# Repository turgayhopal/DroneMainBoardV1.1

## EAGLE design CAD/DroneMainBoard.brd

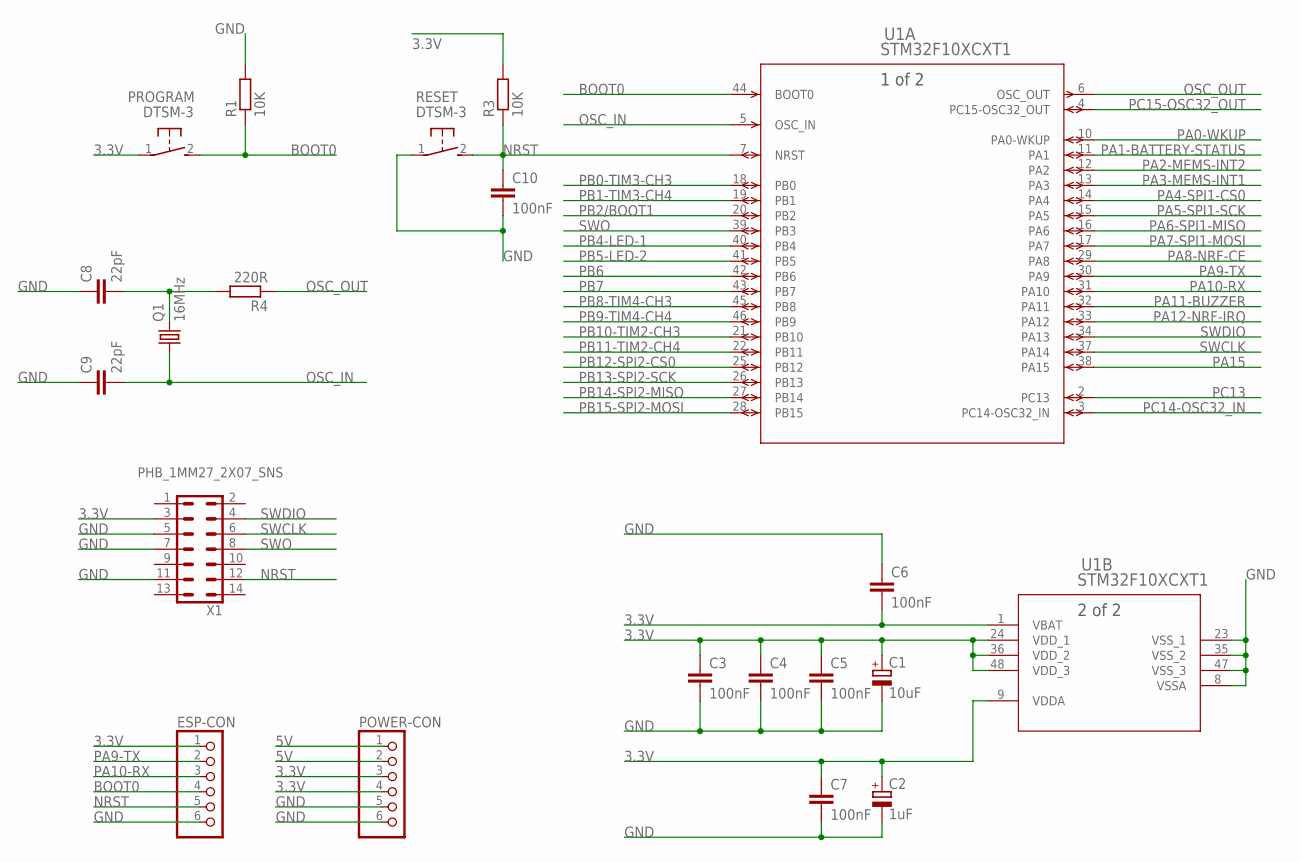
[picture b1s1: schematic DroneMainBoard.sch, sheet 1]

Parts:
C1: 10uF; SMC_A
C2: 1uF; SMC_A
C3, C4, C5, C6, C7, C10: 100nF; C0603
C8, C9: 22pF; C0603
ESP-CON: PINHD-1X6; 1X06
POWER-CON: PINHD-1X6; 1X06
PROGRAM: DTSM-3
Q1: 16MHz; HC49/S
R1, R3: 10K; R0603
R4: 220R; R0603
RESET: DTSM-3
U1: STM32F10XCXT1; LQFP48-7X7MM
X1: PHB_1MM27_2X07_SNS

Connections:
3.3V: C1.+, C2.+, C3.1, C4.1, C5.1, C6.2, C7.1, ESP-CON.1, POWER-CON.3, POWER-CON.4, PROGRAM.1, R3.2, U1.1 (VBAT), U1.9 (VDDA), U1.24 (VDD_1), U1.36 (VDD_2), U1.48 (VDD_3), X1.3; also elsewhere on the board
5V: POWER-CON.1, POWER-CON.2; also elsewhere on the board
BOOT0: ESP-CON.4, PROGRAM.2, R1.1, U1.44 (BOOT0)
GND: C1.-, C2.-, C3.2, C4.2, C5.2, C6.1, C7.2, C8.1, C9.1, C10.2, ESP-CON.6, POWER-CON.5, POWER-CON.6, R1.2, RESET.1, U1.8 (VSSA), U1.23 (VSS_1), U1.35 (VSS_2), U1.47 (VSS_3), X1.5, X1.7, X1.11; also elsewhere on the board
unnamed: C8.2, Q1.2, R4.2
NRST: C10.1, ESP-CON.5, R3.1, RESET.2, U1.7 (NRST), X1.12
OSC_IN: C9.2, Q1.1, U1.5 (OSC_IN)
OSC_OUT: R4.1, U1.6 (OSC_OUT)
PA0-WKUP: U1.10 (PA0-WKUP)
PA1-BATTERY-STATUS: U1.11 (PA1); also elsewhere on the board
PA2-MEMS-INT2: U1.12 (PA2); also elsewhere on the board
PA3-MEMS-INT1: U1.13 (PA3); also elsewhere on the board
PA4-SPI1-CS0: U1.14 (PA4); also elsewhere on the board
PA5-SPI1-SCK: U1.15 (PA5); also elsewhere on the board
PA6-SPI1-MISO: U1.16 (PA6); also elsewhere on the board
PA7-SPI1-MOSI: U1.17 (PA7); also elsewhere on the board
PA8-NRF-CE: U1.29 (PA8); also elsewhere on the board
PA9-TX: ESP-CON.2, U1.30 (PA9)
PA10-RX: ESP-CON.3, U1.31 (PA10)
PA11-BUZZER: U1.32 (PA11); also elsewhere on the board
PA12-NRF-IRQ: U1.33 (PA12); also elsewhere on the board
PA15: U1.38 (PA15)
PB0-TIM3-CH3: U1.18 (PB0)
PB1-TIM3-CH4: U1.19 (PB1)
PB2/BOOT1: U1.20 (PB2)
PB4-LED-1: U1.40 (PB4); also elsewhere on the board
PB5-LED-2: U1.41 (PB5); also elsewhere on the board
PB6: U1.42 (PB6)
PB7: U1.43 (PB7)
PB8-TIM4-CH3: U1.45 (PB8); also elsewhere on the board
PB9-TIM4-CH4: U1.46 (PB9); also elsewhere on the board
PB10-TIM2-CH3: U1.21 (PB10); also elsewhere on the board
PB11-TIM2-CH4: U1.22 (PB11); also elsewhere on the board
PB12-SPI2-CS0: U1.25 (PB12); also elsewhere on the board
PB13-SPI2-SCK: U1.26 (PB13); also elsewhere on the board
PB14-SPI2-MISO: U1.27 (PB14); also elsewhere on the board
PB15-SPI2-MOSI: U1.28 (PB15); also elsewhere on the board
PC13: U1.2 (PC13)
PC14-OSC32_IN: U1.3 (PC14-OSC32_IN)
PC15-OSC32_OUT: U1.4 (PC15-OSC32_OUT)
SWCLK: U1.37 (PA14), X1.6
SWDIO: U1.34 (PA13), X1.4
SWO: U1.39 (PB3), X1.8

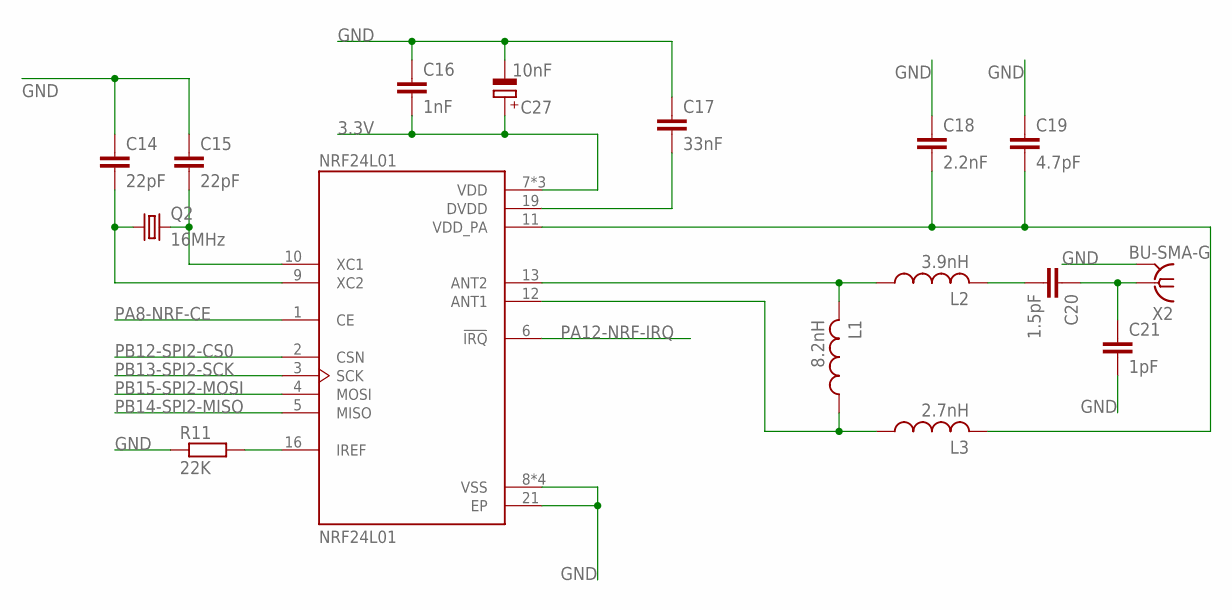
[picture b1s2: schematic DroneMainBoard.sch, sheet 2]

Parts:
C14, C15: 22pF; C0603
C16: 1nF; C0603
C17: 33nF; C0603
C18: 2.2nF; C0603
C19: 4.7pF; C0603
C20: 1.5pF; C0603
C21: 1pF; C0603
C27: 10nF; SMC_A
L1: 8.2nH; L2012C
L2: 3.9nH; L2012C
L3: 2.7nH; L2012C
NRF24L01: NRF24L01; QFN50P400X400X95-21N
Q2: 16MHz; HC49/S
R11: 22K; R0603
X2: BU-SMA-G

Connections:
3.3V: C16.2, C27.+, NRF24L01.7 (VDD), NRF24L01.15 (VDD), NRF24L01.18 (VDD); also elsewhere on the board
GND: C14.1, C15.1, C16.1, C17.1, C18.1, C19.1, C21.2, C27.-, NRF24L01.8 (VSS), NRF24L01.14 (VSS), NRF24L01.17 (VSS), NRF24L01.20 (VSS), NRF24L01.21 (EP), R11.1, X2.2, X2.3 (2), X2.4 (2), X2.5 (2); also elsewhere on the board
unnamed: NRF24L01.16 (IREF), R11.2
unnamed: C17.2, NRF24L01.19 (DVDD)
unnamed: L1.2, L2.1, NRF24L01.13 (ANT2)
unnamed: L1.1, L3.1, NRF24L01.12 (ANT1)
unnamed: C18.2, C19.2, L3.2, NRF24L01.11 (VDD_PA)
unnamed: C14.2, NRF24L01.9 (XC2), Q2.1
unnamed: C15.2, NRF24L01.10 (XC1), Q2.2
unnamed: C20.1, C21.1, X2.1
unnamed: C20.2, L2.2
PA8-NRF-CE: NRF24L01.1 (CE); also elsewhere on the board
PA12-NRF-IRQ: NRF24L01.6 (!IRQ); also elsewhere on the board
PB12-SPI2-CS0: NRF24L01.2 (CSN); also elsewhere on the board
PB13-SPI2-SCK: NRF24L01.3 (SCK); also elsewhere on the board
PB14-SPI2-MISO: NRF24L01.5 (MISO); also elsewhere on the board
PB15-SPI2-MOSI: NRF24L01.4 (MOSI); also elsewhere on the board

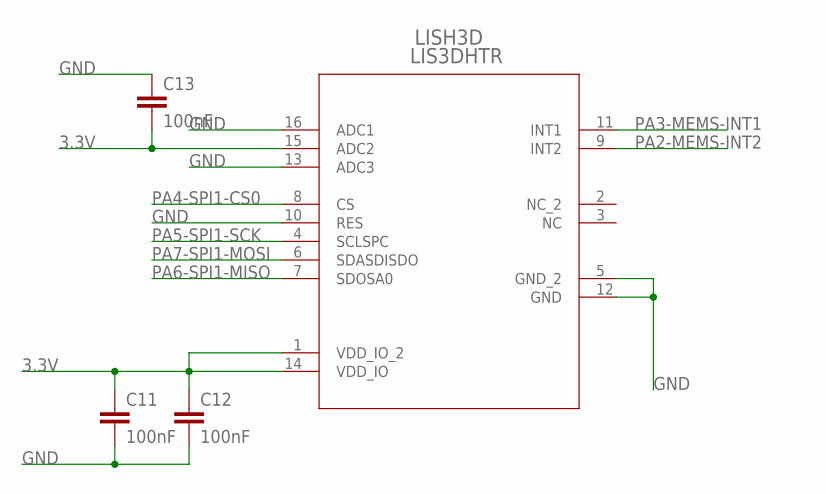
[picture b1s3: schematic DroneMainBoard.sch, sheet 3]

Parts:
C11, C12, C13: 100nF; C0603
LISH3D: LIS3DHTR; LGA-16_3X3X1MM_STM

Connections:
3.3V: C11.1, C12.1, C13.2, LISH3D.1 (VDD_IO_2), LISH3D.14 (VDD_IO), LISH3D.15 (ADC2); also elsewhere on the board
GND: C11.2, C12.2, C13.1, LISH3D.5 (GND_2), LISH3D.10 (RES), LISH3D.12 (GND), LISH3D.13 (ADC3), LISH3D.16 (ADC1); also elsewhere on the board
PA2-MEMS-INT2: LISH3D.9 (INT2); also elsewhere on the board
PA3-MEMS-INT1: LISH3D.11 (INT1); also elsewhere on the board
PA4-SPI1-CS0: LISH3D.8 (CS); also elsewhere on the board
PA5-SPI1-SCK: LISH3D.4 (SCLSPC); also elsewhere on the board
PA6-SPI1-MISO: LISH3D.7 (SDOSA0); also elsewhere on the board
PA7-SPI1-MOSI: LISH3D.6 (SDASDISDO); also elsewhere on the board

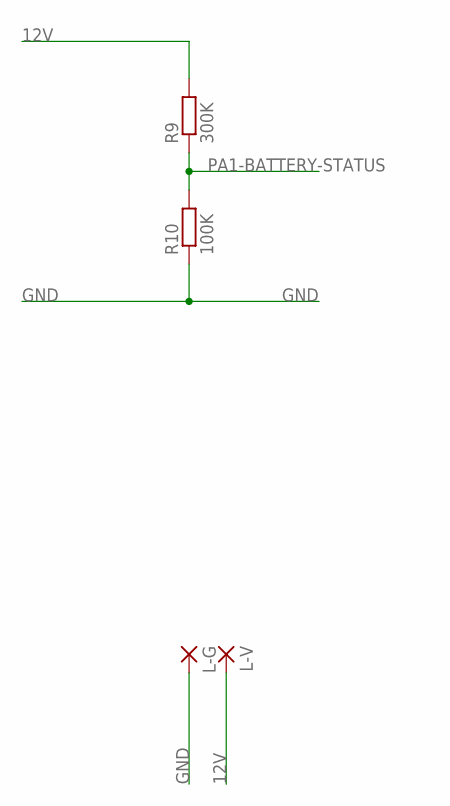
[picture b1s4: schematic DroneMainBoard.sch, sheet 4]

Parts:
L-G: 2,54/1,1
L-V: 2,54/1,1
R9: 300K; R0603
R10: 100K; R0603

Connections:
12V: L-V.1, R9.2
GND: L-G.1, R10.1; also elsewhere on the board
PA1-BATTERY-STATUS: R9.1, R10.2; also elsewhere on the board

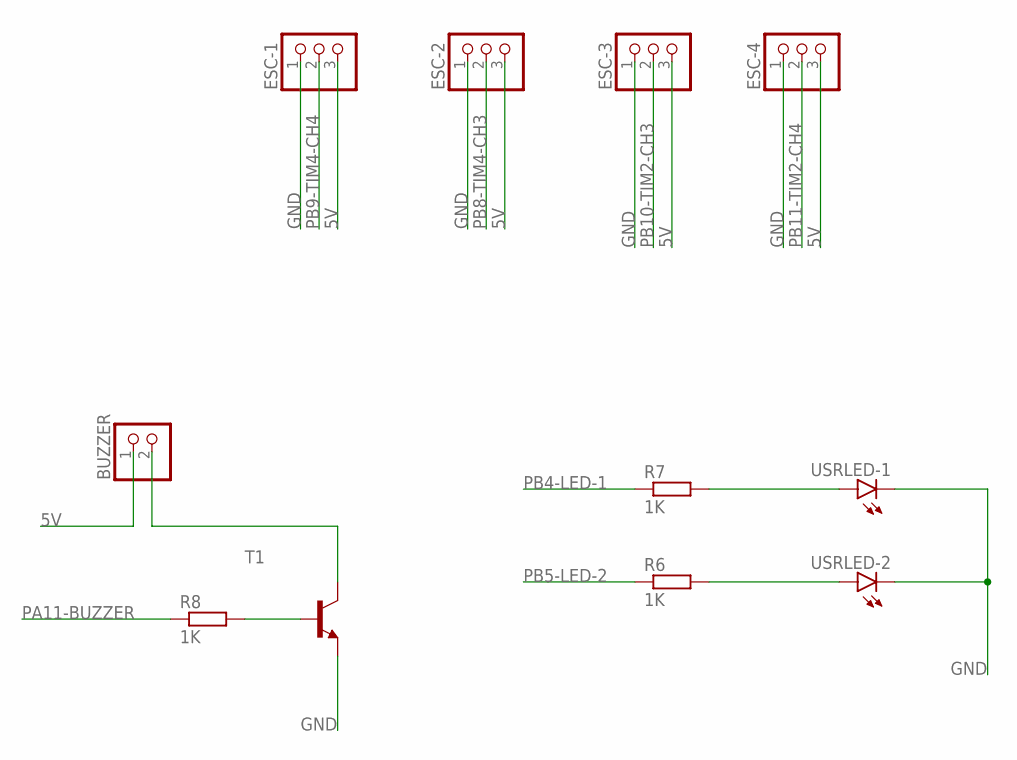
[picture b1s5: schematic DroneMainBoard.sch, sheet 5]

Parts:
BUZZER: PINHD-1X2; 1X02
ESC-1, ESC-2, ESC-3, ESC-4: PINHD-1X3; 1X03
R6, R7, R8: 1K; R0603
T1: MMBT3904LT1-NPN-SOT23-BEC; SOT23-BEC
USRLED-1, USRLED-2: LEDCHIP-LED0805; CHIP-LED0805

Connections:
5V: BUZZER.1, ESC-1.3, ESC-2.3, ESC-3.3, ESC-4.3; also elsewhere on the board
GND: ESC-1.1, ESC-2.1, ESC-3.1, ESC-4.1, T1.E, USRLED-1.C, USRLED-2.C; also elsewhere on the board
unnamed: R6.2, USRLED-2.A
unnamed: R7.2, USRLED-1.A
unnamed: BUZZER.2, T1.C
unnamed: R8.2, T1.B
PA11-BUZZER: R8.1; also elsewhere on the board
PB4-LED-1: R7.1; also elsewhere on the board
PB5-LED-2: R6.1; also elsewhere on the board
PB8-TIM4-CH3: ESC-2.2; also elsewhere on the board
PB9-TIM4-CH4: ESC-1.2; also elsewhere on the board
PB10-TIM2-CH3: ESC-3.2; also elsewhere on the board
PB11-TIM2-CH4: ESC-4.2; also elsewhere on the board

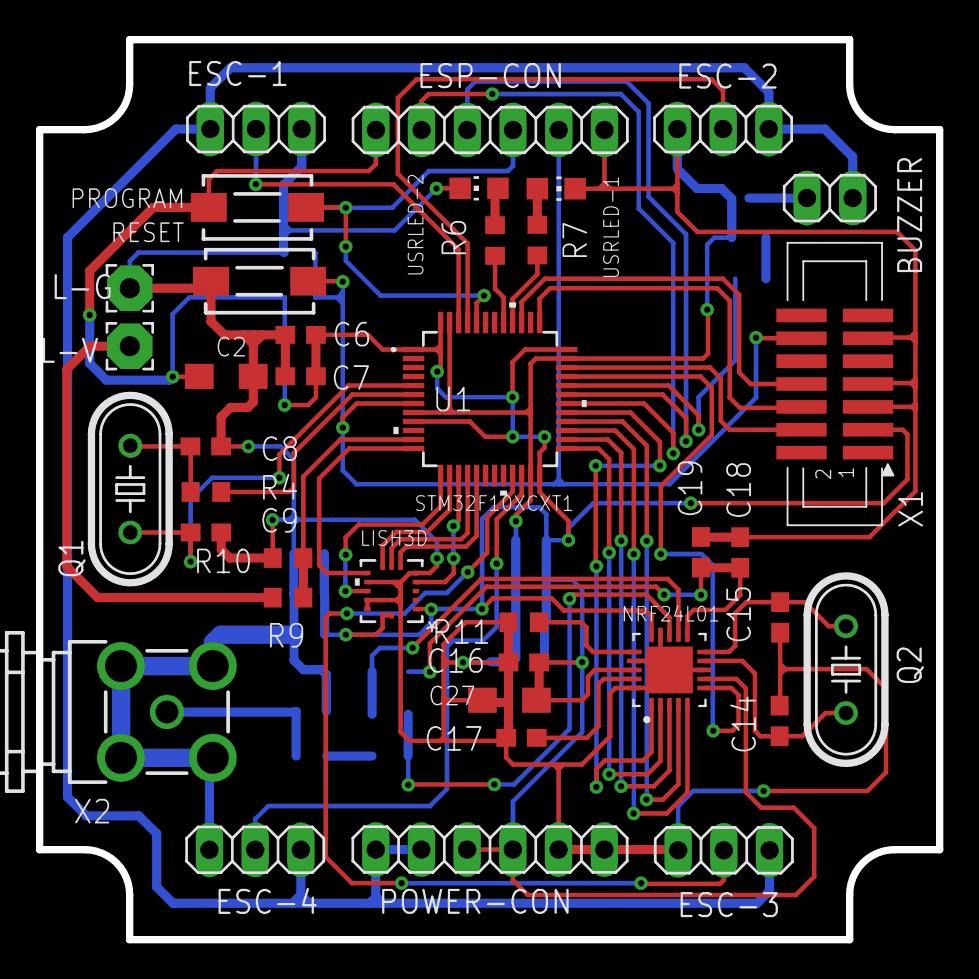
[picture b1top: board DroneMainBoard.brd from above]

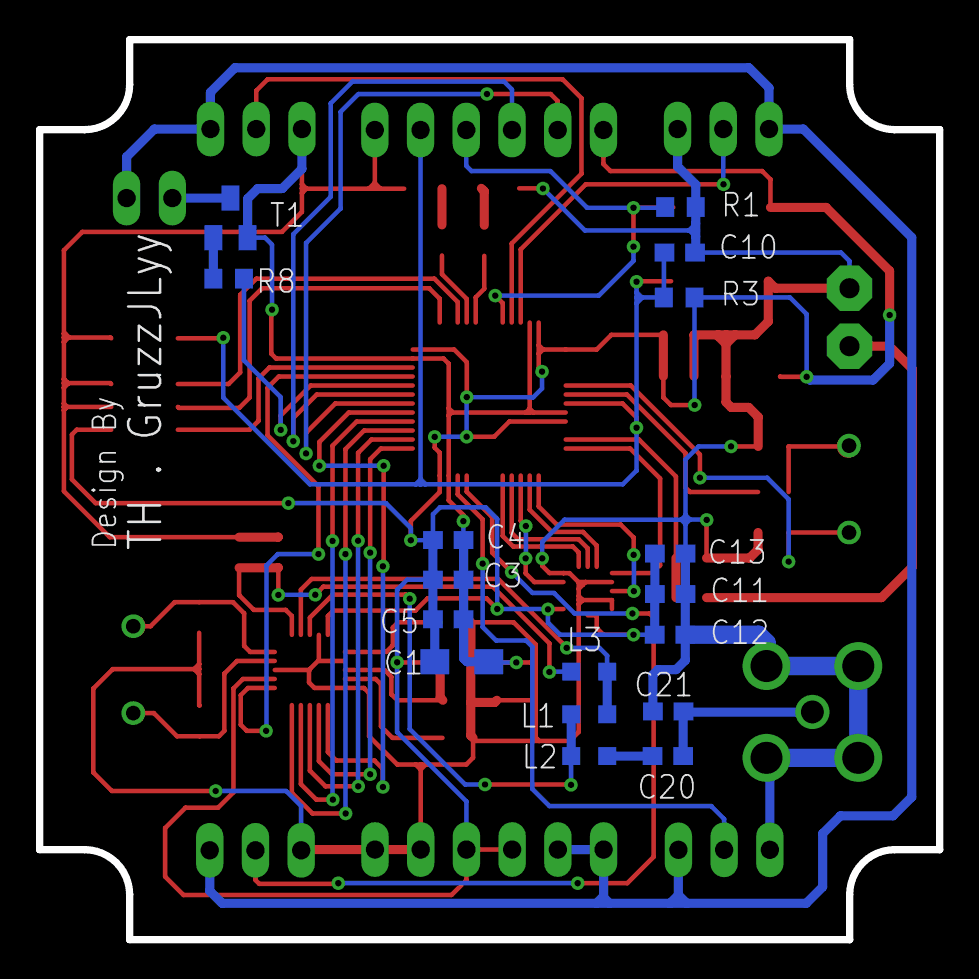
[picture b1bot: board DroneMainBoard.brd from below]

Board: 2 copper layers, 50.0 x 50.0 mm, 55 parts (17 on the bottom side), 47 nets.

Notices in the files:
parts and their libraries:
COPYRIGHT: Copyright (C) 2016 Accelerated Designs. All rights reserved
